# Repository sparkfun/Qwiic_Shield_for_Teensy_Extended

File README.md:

# Qwiic_Shield_for_Teensy_Extended
This is a shield that connects the I2C bus on an extended form factor Teensy to Qwiic connectors.

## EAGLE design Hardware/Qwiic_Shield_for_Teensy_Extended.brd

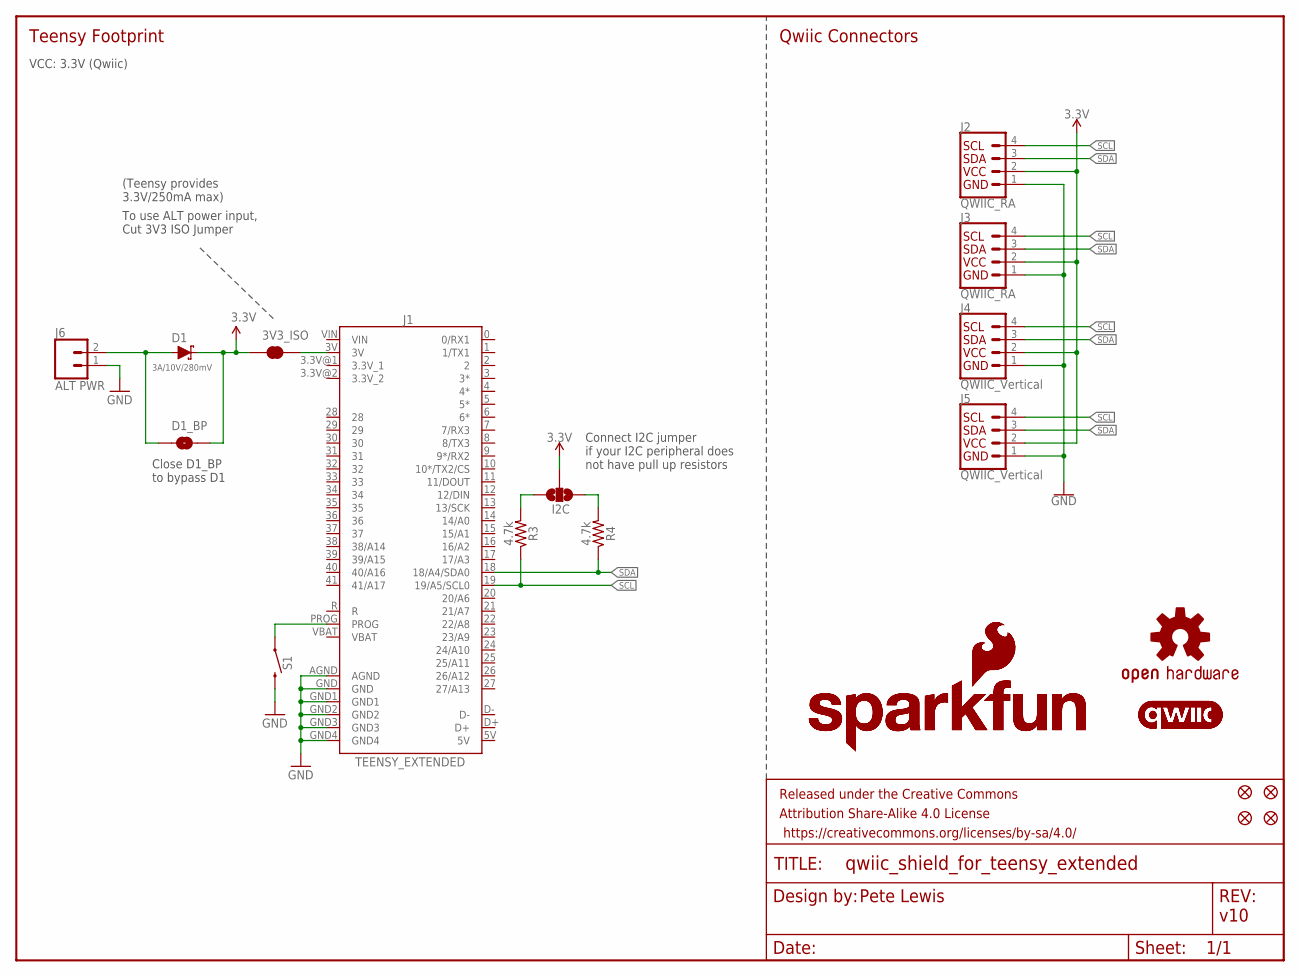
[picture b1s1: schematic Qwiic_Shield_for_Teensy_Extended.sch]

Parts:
3V3_ISO: JUMPER-SMT_2_NC_TRACE_SILK; SMT-JUMPER_2_NC_TRACE_SILK
D1: 3A/10V/280mV; SOD-323
D1_BP: JUMPER-SMT_2_NO_SILK; SMT-JUMPER_2_NO_SILK
FD1, FD2, FD3, FD4: FIDUCIAL1X2; FIDUCIAL-1X2
FRAME1: FRAME-LETTER; CREATIVE_COMMONS
I2C: JUMPER-SMT_3_NO_SILK; SMT-JUMPER_3_NO_SILK
J1: TEENSY_EXTENDED; TEENSY_EXTENDED_NO_SILK
J2, J3: QWIIC_RA; JST04_1MM_RA
J4, J5: QWIIC_Vertical; JST04_1MM_VERT
J6: ALT PWR; 1X02_NO_SILK
LOGO1, LOGO2: SFE_LOGO_NAME_FLAME.1_INCH; SFE_LOGO_NAME_FLAME_.1
LOGO3: OSHW-LOGOS; OSHW-LOGO-S
LOGO4, LOGO5: QWIIC_LOGO_5MM; QWIIC_5MM
R3, R4: 4.7k; 0603
S1: SMD_5.2MM; TACTILE_SWITCH_SMD_5.2MM

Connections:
3.3V: 3V3_ISO.1, D1.C, D1_BP.2, I2C.2, J2.2, J3.2, J4.2, J5.2
3.3V_1: J1.3.3V@1 (3.3V_1)
3.3V_2: J1.3.3V@2 (3.3V_2)
5V: J1.5V
D+: J1.D+
D-: J1.D-
GND: J1.AGND, J1.GND, J1.GND1, J1.GND2, J1.GND3, J1.GND4, J2.1, J3.1, J4.1, J5.1, J6.1, S1.3 (2)
unnamed: I2C.3, R4.2
unnamed: I2C.1, R3.2
unnamed: 3V3_ISO.2, J1.3V
unnamed: D1.A, D1_BP.1, J6.2
unnamed: J1.PROG, S1.1
SCL: J1.19 (19/A5/SCL0), J2.4, J3.4, J4.4, J5.4, R3.1
SDA: J1.18 (18/A4/SDA0), J2.3, J3.3, J4.3, J5.3, R4.1
VBAT: J1.VBAT
VIN: J1.VIN

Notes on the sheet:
Pete Lewis
v10
Teensy Footprint
Qwiic Connectors
VCC: 3.3V (Qwiic)
(Teensy provides 3.3V/250mA max)
Connect I2C jumper if your I2C peripheral does not have pull up resistors
To use ALT power input, Cut 3V3 ISO Jumper
Close D1_BP to bypass D1

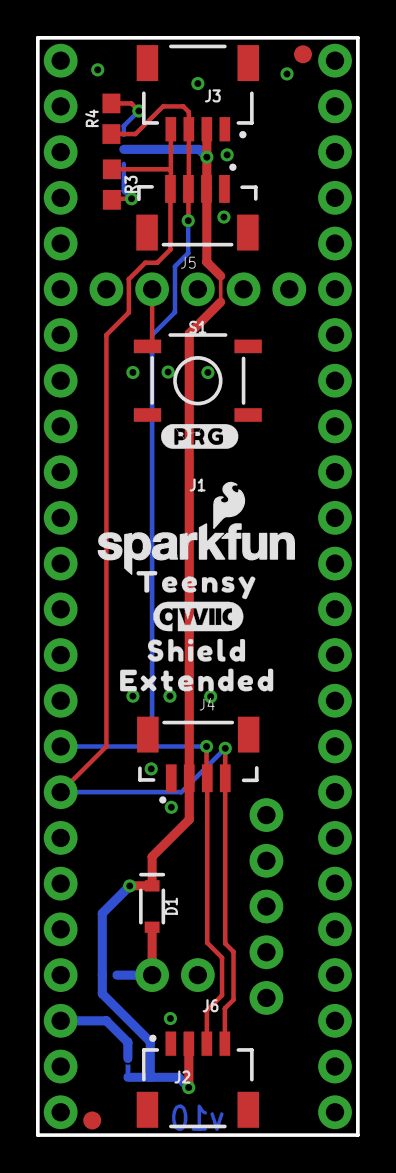
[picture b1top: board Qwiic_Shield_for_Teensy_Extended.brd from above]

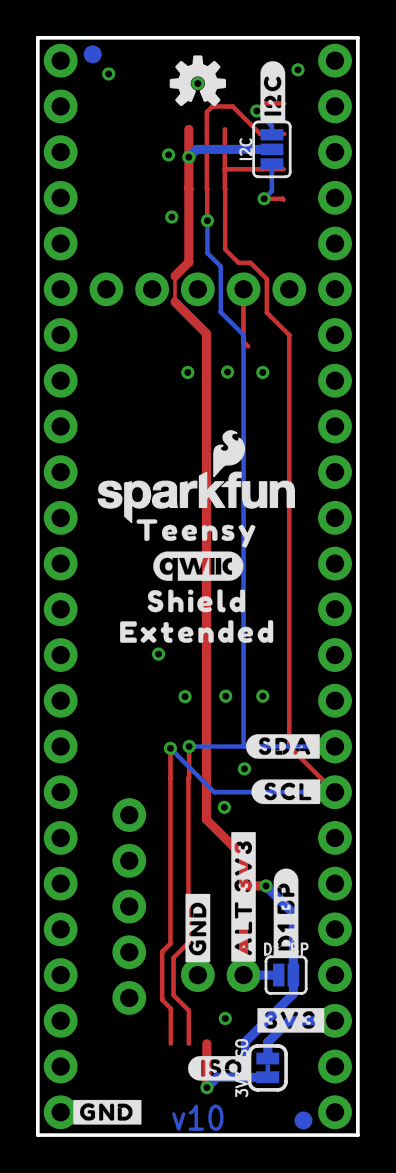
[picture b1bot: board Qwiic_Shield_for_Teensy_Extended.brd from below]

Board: 2 copper layers, 17.8 x 61.0 mm, 40 parts (20 on the bottom side), 9 nets.

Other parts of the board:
U$1: #I2C#0
U$2, U$13: TEENSY0
U$3: 3V36
U$4: #D1_BP#0
U$5: #ALT_3V3#0
U$6: #PRG#0
U$7, U$9: #GND#0
U$8, U$12: SHIELD0
U$10: #ISO#0
U$11, U$16: EXTENDED0
U$15: #3V3#0
U$18: #SDA#0
U$19: #SCL#0

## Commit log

2020-09-02 separating design into "normal" and extended version with separate repos
2020-09-02 checklist run post design review
    -adjusted values for better assembly sheet
2020-09-03 Measures correction
    -removed old measures that were left over from short version
    -straightened the measure for the middle-bottom qwiic connector that was ever so slightly off.
2020-09-04 Production panel v10
2020-09-10 Dimensional drawings
    -also added a couplt more measures to brd file
2020-09-10 squaring up image for better sizing in tutorial
2020-10-13 Update README
    Updating README to add photos and relevant links along with updated description.
2020-11-05 migrated teensy part to SparkFun-Boards.lbr

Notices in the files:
parts and their libraries:
SparkFun-Aesthetics: Licensing: Creative Commons ShareAlike 4.0 International - https://creativecommons.org/licenses/by-sa/4.0
SparkFun-Aesthetics: Released under the Creative Commons Attribution Share-Alike 4.0 License
SparkFun-Aesthetics: https://creativecommons.org/licenses/by-sa/4.0
